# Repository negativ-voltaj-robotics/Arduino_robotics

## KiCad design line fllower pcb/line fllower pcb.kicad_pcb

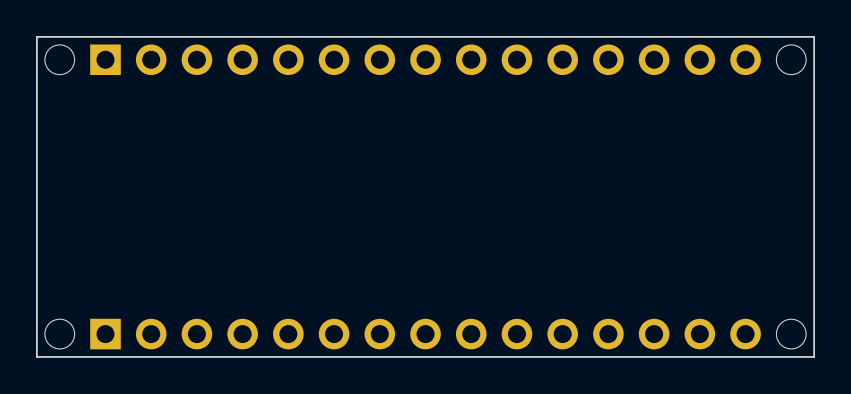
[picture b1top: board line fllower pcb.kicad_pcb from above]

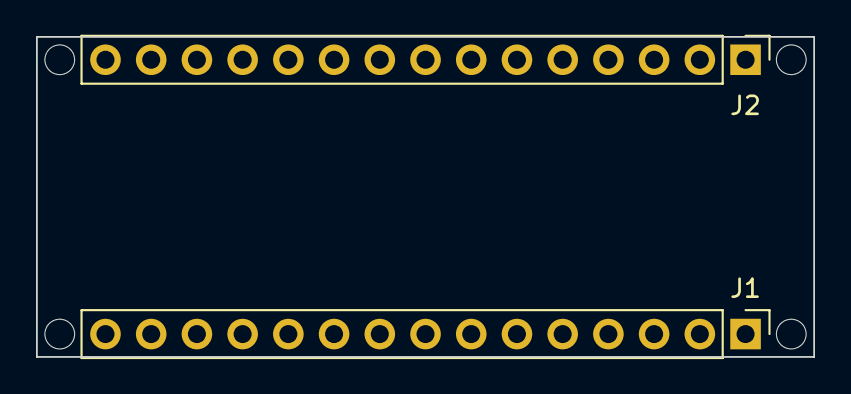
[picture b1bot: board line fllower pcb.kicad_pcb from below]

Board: 2 copper layers, 43.2 x 17.8 mm, 6 parts (2 on the bottom side), 2 nets, no tracks yet.

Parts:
J1: Analog; PinHeader_1x15_P2.54mm_Vertical
J2: Digital; PinHeader_1x15_P2.54mm_Vertical
MH1, MH2, MH3, MH4: MountingHole_65mil

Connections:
/~RESET: J1.13, J2.13
GND: J1.14, J2.12
